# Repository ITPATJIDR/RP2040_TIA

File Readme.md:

# RP2040 Transimpedance Amplifier

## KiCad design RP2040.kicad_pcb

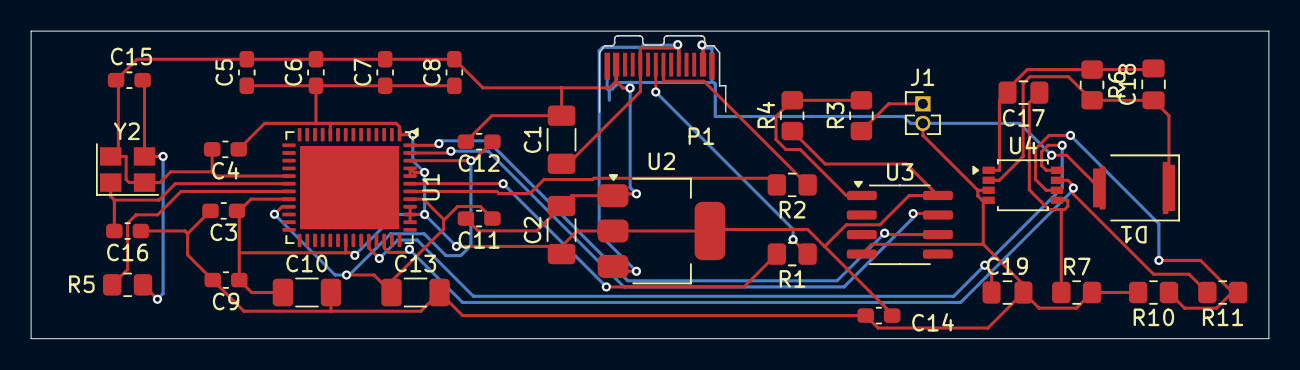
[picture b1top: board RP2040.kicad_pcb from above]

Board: 2 copper layers, 80.5 x 20.0 mm, 36 parts (0 on the bottom side), 22 nets.

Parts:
C1, C2: 10u; C_1206_3216Metric_Pad1.33x1.80mm_HandSolder
C3, C4, C5, C6, C7, C8, C9, C11, C12, C14: 100n; C_0603_1608Metric_Pad1.08x0.95mm_HandSolder
C10, C13: 1u; C_1206_3216Metric_Pad1.33x1.80mm_HandSolder
C15, C16: 15p; C_0603_1608Metric_Pad1.08x0.95mm_HandSolder
C17: 150nF; C_0805_2012Metric_Pad1.18x1.45mm_HandSolder
C18: 15pF; C_0805_2012Metric_Pad1.18x1.45mm_HandSolder
C19: 100nF; C_0805_2012Metric_Pad1.18x1.45mm_HandSolder
D1: SFH206K; Osram_SFH2201
J1: Conn_01x02; PinHeader_1x02_P1.27mm_Vertical
P1: USB_C_Plug_USB2.0; USB_C_Plug_JAE_DX07P024AJ1
R1, R2, R3, R5, R6, R7, R10, R11: 1K; R_0805_2012Metric_Pad1.20x1.40mm_HandSolder
R4: 10k; R_0805_2012Metric_Pad1.20x1.40mm_HandSolder
U1: RP2040; QFN-52-1EP_7x8mm_P0.5mm_EP5.41x6.45mm
U2: NCP1117-3.3_SOT223; SOT-223-3_TabPin2
U3: W25Q128JVS; SOIC-8_3.9x4.9mm_P1.27mm
U4: LM358; OnSemi_Micro8
Y2: ABM8-272-T3; Crystal_SMD_Abracon_ABM8G-4Pin_3.2x2.5mm

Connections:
+1V1: C11.1, C12.1, C13.1, U1.23 (DVDD), U1.45 (VREG_VOUT), U1.50 (DVDD)
+3V3: C2.1, C3.1, C4.1, C5.1, C6.1, C7.1, C8.1, C9.1, C10.1, C14.1, R4.1, U1.1 (IOVDD), U1.10 (IOVDD), U1.22 (IOVDD), U1.33 (IOVDD), U1.42 (IOVDD), U1.43 (ADC_AVDD), U1.44 (VREG_IN), U1.48 (USB_VDD), U1.49 (IOVDD), U2.2 (VO), U3.8 (VCC)
/5V_IN: C19.1, U1.36 (GPIO24), U4.8 (V+)
/QSPI_SCLK: U1.52 (QSPI_SCLK), U3.6 (CLK)
/QSPI_SD0: U1.53 (QSPI_SD0), U3.5 (DI(IO0))
/QSPI_SD3: U1.51 (QSPI_SD3), U3.7 (IO3)
/QSPI_SS: R3.2, R4.2, U3.1 (~CS)
/USB_BOOT: J1.1, R3.1
/USB_D+: P1.A6 (D+), R1.1
/USB_D-: P1.A7 (D-), R2.1
/VOUT: R11.2, U1.38 (GPIO26_ADC0), U4.7
/XIN: C16.2, U1.20 (XIN), Y2.1
/XOUT: R5.2, U1.21 (XOUT)
GND: C1.2, C2.2, C3.2, C4.2, C5.2, C6.2, C7.2, C8.2, C9.2, C10.2, C11.2, C12.2, C13.2, C14.2, C15.1, C16.1, C19.2, D1.2 (A), J1.2, P1.A1 (GND), P1.A12 (GND), P1.B1 (GND), P1.B12 (GND), P1.S1 (SHIELD), R7.2, R10.2, U1.19 (TESTEN), U2.1 (GND), U3.4 (GND), U4.3 (+), U4.4 (V-), Y2.2, Y2.4
unnamed: C15.2, R5.1, Y2.3
unnamed: C17.2, C18.2, R6.1, U4.1
unnamed: C18.1, D1.1 (K), R6.2, U4.2 (-)
unnamed: R2.2, U1.46 (USB_DM)
unnamed: R1.2, U1.47 (USB_DP)
unnamed: C17.1, R7.1, U4.5 (+)
unnamed: R10.1, R11.1, U4.6 (-)
VBUS: C1.1, P1.A4 (VBUS), P1.A9 (VBUS), P1.B4 (VBUS), P1.B9 (VBUS), U2.3 (VI)

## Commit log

2024-11-04 start: first commit
2024-11-04 fix: read me
